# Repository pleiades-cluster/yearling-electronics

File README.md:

# yearling-electronics
PROVES-Yearling Project files for CD&amp;H and EPS boards

C&DH Board Design Requirements: 
The Command and Data Handling (C&DH) Board is the link between our satellite and the rest of the world. The C&DH board will also handle the broad level scheduling of satellite activities. 

Key Requirements: 

- Facilitate Radio Receive and Transmit 
- Collect Satellite State of Health Data 
- Process Satellite Data into Packets for Transmission 
- Schedule High Level Satellite Activities 

Would be nice: 
- Facilitate a live engineering data link with other processors onboard the satellite 
- EPS Board Design Requirements: 

Non-Optional:
- Overcharge Protection
- Overdischarge Protection
- Solar Charging Circuit 
- 3.3V Regulator
- 5V Regulator 
- Inhibit Scheme 
- Battery Monitor

Very Preferred:
- Direct RP2040 Control On-Board 
- Battery Fuel Gauge 
- Power Path Circuit
- Battery Thermal Management 

Would be Nice:
- Circuit Breaker System 
- Resettable Fuses 

The EPS board will be a hybrid of the PyCubed and OreSat architectures.

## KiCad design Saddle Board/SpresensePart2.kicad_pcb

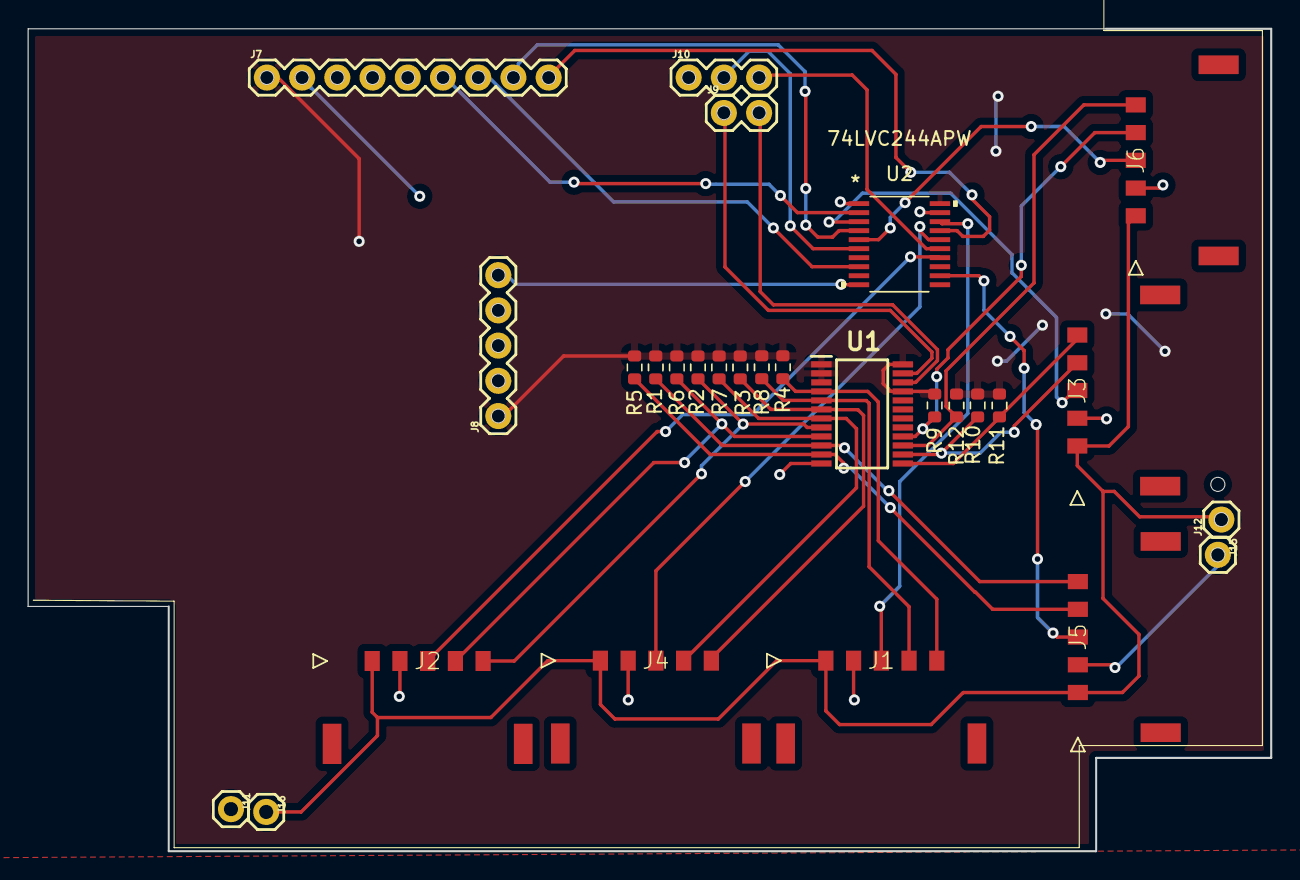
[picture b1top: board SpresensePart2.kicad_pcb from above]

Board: 2 copper layers, 89.6 x 59.3 mm, 28 parts (0 on the bottom side), 29 nets.

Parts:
J1, J2, J3, J4, J5, J6: 5040500591; 2053380005
J7: CONN_09; 1X09
J8: CONN_05; 1X05
J9: CONN_02; 1X02
J10: 455-1750-1-ND; 1X03
J11, J12, J15, J16: CONN_01; 1X01
R1, R2, R3, R4, R5, R6, R7, R8, R9, R10, R11, R12: 10K; R_0603_1608Metric
U1: TCA9548APWR; SOP65P640X120-24N
U2: 74LVC244APW

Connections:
+3V3: J7.1, J8.1, R1.1, R2.1, R3.1, R4.1, R5.1, R6.1, R7.1, R8.1, R9.1, R10.1, R11.1, R12.1, U1.1 (A0), U1.2 (A1), U1.3 (~RESET), U1.21 (A2), U1.24 (VCC), U2.20 (VCC)
/3V30: J1.3, U2.18 (1Y0)
/3V31: J4.3, U2.16 (1Y1)
/3V32: J2.3, U2.14 (1Y2)
/3V33: J5.3, U2.12 (1Y3)
/3V34: J3.3, U2.3 (2Y0)
/3V35: J6.3, U2.5 (2Y1)
/PA16: J9.2, U1.22 (SCL)
/PA17: J9.1, U1.23 (SDA)
/PA19: J10.3, U2.15 (2A1)
/PA20: J7.8, U2.4 (1A1)
/PA22: J7.9, U2.17 (2A0)
/PB16: J10.2, U2.6 (1A2)
/PB22: J7.7, U2.8 (1A3)
/PB23: J7.6, U2.2 (1A0)
/SC0: J1.4, R8.2, U1.5 (SC0)
/SC1: J4.4, R7.2, U1.7 (SC1)
/SC2: J2.4, R6.2, U1.9 (SC2)
/SC3: J5.4, R5.2, U1.11 (SC3)
/SC4: J3.4, R10.2, U1.14 (SC4)
/SC5: J6.4, R9.2, U1.16 (SC5)
/SD0: J1.5, R4.2, U1.4 (SD0)
/SD1: J4.5, R3.2, U1.6 (SD1)
/SD2: J2.5, R2.2, U1.8 (SD2)
/SD3: J5.5, R1.2, U1.10 (SD3)
/SD4: J3.5, R11.2, U1.13 (SD4)
/SD5: J6.5, R12.2, U1.15 (SD5)
/VSOLAR: J1.1, J2.1, J3.1, J4.1, J5.1, J6.1, J12.1, J16.1
GND: J1.2, J2.2, J3.2, J4.2, J5.2, J6.2, J7.2, J8.5, J11.1, J15.1, U1.12 (GND), U2.1 (1OE*), U2.10 (GND), U2.19 (2OE*)

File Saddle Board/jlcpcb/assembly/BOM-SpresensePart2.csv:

Comment,Designator,Footprint,LCSC
CONN_01,J16,1X01,
74LVC244APW,U2,74LVC244APW,
10K,R6,R_0603_1608Metric,
10K,R4,R_0603_1608Metric,
CONN_09,J7,1X09,
CONN_02,J9,1X02,
TCA9548APWR,U1,SOP65P640X120-24N,
5040500591,J2,2053380005,
CONN_05,J8,1X05,
10K,R5,R_0603_1608Metric,
455-1750-1-ND,J10,1X03,
10K,R3,R_0603_1608Metric,
10K,R7,R_0603_1608Metric,
5040500591,J3,2053380005,
10K,R11,R_0603_1608Metric,
10K,R8,R_0603_1608Metric,
5040500591,J6,2053380005,
10K,R1,R_0603_1608Metric,
CONN_01,J11,1X01,
10K,R10,R_0603_1608Metric,
10K,R12,R_0603_1608Metric,
5040500591,J1,2053380005,
5040500591,J4,2053380005,
5040500591,J5,2053380005,
10K,R2,R_0603_1608Metric,
CONN_01,J12,1X01,
CONN_01,J15,1X01,
10K,R9,R_0603_1608Metric,

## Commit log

2022-04-05 Added 18650 Batteries and protection circuit
2022-04-11 Initial Commit
    All of the Eagle Files from Antony's V1a OneDrive Folder
2022-04-15 Add files via upload
    im so sorry for the million V0 backup files XD this has the 'V1" schem with new solar and ADC ckt
2022-04-15 EPS V1.5
    Major file cleanup, combined V1 files from Christeen and Austin, added gitignore to remove backup and extra files.
2022-04-15 Quick Cleanup
    Added ToDo's, not much else need sleep
2022-04-15 Added 5V Reg and Heater
2022-04-15 Edited ToDo's
    99% of features are now implemented, need to clean up nets and add footprints for MPPT IC's.
    Then ready for layout!
2023-02-01 Saddle Board
2023-02-01 Final As Ordered Feb 1, 2023

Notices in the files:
parts and their libraries:
Copyright 2021 Accelerated Designs. All rights reserved.
